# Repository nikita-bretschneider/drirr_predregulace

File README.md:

# Poznámky k návrhu desky skokové předregulace

## Změny v konstrukci

Konstrukce není moje. Hodnoty součástek jsou uvedeny pouze tam, kde byly známy (platí pro schéma i silkscreeny). Jediná konstrukční změna je přidání tranzistoru *Q1*, protože proudová zatížitelnost výstupu *LM311* je pouze *50mA*, což stačí na malé relé, avšak chci otevřít možnost použít automobilní relé, jehož pozitivní vlastností je že se nerozteče při trvalém sepnutí. Bohužel si dokáže vzít až *140mA*. PNP tranzistor používám z toho důvodu, aby nebylo nutno měnit logiku spínání. *LM311* sama o sobě spíná v záporném pólu, pokud se aktivuje spínání tranzistorem, spíná se v kladném pólu, vlastní *LM311* spíná pouze bázový proud tranzistoru *Q1*. Použití tohoto tranzistoru je optional a konfiguruje se při osazení propojkami *J4*, *J5* a *J6*. Původní zapojení, tj. bez tranzistoru *Q1*, se aktivuje neosazením *Q1* a *R6*, dále se spojí *J5* a *J6*. Propojka *J4* zůstává rozpojená. Pro použití tranzistoru *Q1* (například při použití automobilního relé) se osadí *R6*, *Q1* a propojí se propojka *J4*. Propojky *J5* a *J6* zůstávají rozpojené.

## Použití pojmenovaných signálů a propojovací definice

Použití pojmenovaných signálů umožňuje rozdělit schéma do funkčních bloků a tak jej zpřehlednit. Separátní definice připojovacích míst k signálům umožňuje snadno měnit pinout jednotlivých konektorů s ohledem na situaci na desce, neb docházelo k optimalizaci na snadnou výrobu a minimální cenu desky. Dále takový postup vytváří přehledný pinout všech použitých konektorů na jediném místě dokumentace, což opět poslouží přehlednosti.

## Vlastní návrh desky, možné problémy, prokovy

Vlastní návrh desky je proveden tak, aby byl výrobně jednoduchý. Desku lze nechat vyrobit jak s prokovy tak bez nich. V obou případech lze za slabé místo považovat kondenzátory *C1* a *C2*, kde je jeden z pólů přístupný do rozlité země (vedení *ACS0*) pouze přes prokov. Vzhledem k zátěži celého pomocného zdroje řádově ve stovkách mA (a z toho plynoucích cirkulačních proudů maximálně ve stovkách mA) to nepovažuji za problém. Větší problém nastává při pájení *C1* a *C2* do desky bez prokovů, kde nelze pájet z horní strany kvůli překrytí vrstvý pouzdrem součástky. Pro tento případ je na spodní straně připravena rozlitá plocha mědi, kdy lze provést propojení s vrchní stranou (stranou součástek) pomocí vývodů jiných součástek, případně na vhodném místě navrtat via.

Desku lze též vyrobit svépomocí, kdy se strana spojů vyrobí například metodou *toner transfer*, přičemž horní strana obsahuje toliko rozlitou měď (s vyjímkou jednoho jumperu, který lze ignorovat, viz níže), čili před leptáním se vykryjí problematická místa (pod pojistkami a pod částmi konektorů) lakýrnickou páskou, celou horní strana se poté přestříká leptuvzdorným lakem a po zaschnutí se odstraní lakýrnická páska. Pro spodní stranu se použije buď metoda toner transfer, nebo fotocesta. V případě toner transferu doporučuji začít spodní stranou, v případě fotocesty doporučuji obrácený postup.  Po odleptání a odvrtání ze spodní strany se z horní  strany následně odstraní měděná plocha v okolí děr buď odfrézováním, nebo zcela jednoduše pomocí mělkého odvrtání tlustým vrtákem. Neodvrtávají se místa, kde je součástka spojena se zemní plochou. V těchto místech se potom pájí z obou stran. Problémem jednoduché výroby je jumper *J4*, který  je ze stramy součástek a při prostém ponechání měděné vrstvy jednoduše nebude existovat. Nepovažuji to však za problém, protože konfigurace se provádí při osazení a později ji již není možné změnit, čili pokud se osazuje *Q1*, potom se neodfrézuje/neodvrtá měděná vrstva kolem anody *D8* a tato se připájí z obou stran. *J6* a *J5* se potom neosazuje. V opačném případě se okolí anody *D8* odfrézuje, *Q1* a *R6* se neosadí, *D8* se zapájí jen z jedné strany a propojí se *J6* a *J5*.

## Proč není na desce relé

Protože otevřenost variabilitě, protože míním použít automobilní relé, které má vlastní držák a vývody na fastonech, v neposlední řadě proto, že se tím zmenší deska. Navíc to vytváří určitou variabilitu v zapojení předregulace, tj. lze například přepínat mezi dvoucestným usměrněním a násobičem, což otevírá možnost použít transformátor, který náhodou máte, namísto nákupu nějakého konkrétního. Celá deska je navrhovaná s ohledem na maximální možnou variabilitu, je zcela nevhodná pro seriovou výrobu včetně maloseriové, takže je pochopitelně nevhodná i pro strojové osazení.

## Proč se používají svorkovnice

V původní konstrukci byly fastony a osobně v nich vidím problém. Ten konektor chce značnou sílu pro zapojení i vypojení, přičemž tato deska byla navrhovaná nejen na maximální variabilitu, ale také na možnost snadné výroby, do které musím bohužel zahrnout nejen pochybné lamináty, ale též kuprokart a jiné hrůzy. Kombinace kuprokartu a fastonu znamená zlomenou desku. Spolehlivě. Svorkovnice ale funguje, protože se na desku příliš netlačí. Pochopitelně na jejím místě lze osadit víceméně leccos, co roztečí odpovídá. Svorkovnice jsou na desce dvě čtyřpólové a jedna dvoupólová. Spojit je všechny do jedné velké svorkovnice není dobrý nápad, toner transfer občas způsobí mírné ujetí rozměrů, což by pro tak velký pevný kus bylo fatální. Svorkovice je tedy rozdělena na tři logické části — propojení s řídící deskou zdroje, čili pomocné napájení *±12V* a *sense* vstup, svorkovnici pro připojení cívky relé a svorkovnici pro připojení pomocného transformátoru. Tato je zvolena čtyřpinová ze dvou důvodů. Především dvoupinové svorkovnice lze stohovat na čtyřpólové, takže tato volba znamená, že koupíte pět dvoupólových (a dostanete množstevní slevu, což by vás při nákupu jedné třípólové nepotkalo), dále transformátor může mít dvě oddělená sekundární vinutí, proto je střed vyveden dvakrát.

## Použití pomocného transformátoru s jediným sekundárním vinutím

Pokud máte pomocný transformátor jen s jediným vinutím bez vyvedeného středu, neosadí se *F1*, *D1*, *D4* a polovina svorkovnice *J3*. Dále je nutno zvětšit kapacity *C1* a *C2* na minimálně dvojnásobek.Transformátor potom pracuje v lichých půlvlnách do jedné větve a v sudých do druhé. Toto řešení však příliš nedoporučuji.

## Závěr, varování

Konstrukce není moje, desky nevyrábím, pokud si někde chcete zadat výrobu, je to váš problém, odmítám za to nést jakoukoliv odpovědnost. Chyby se stávají, to je realita. Vše si důkladně zkontrolujte a rozmyslete před tím, než začnete desku vyrábět.

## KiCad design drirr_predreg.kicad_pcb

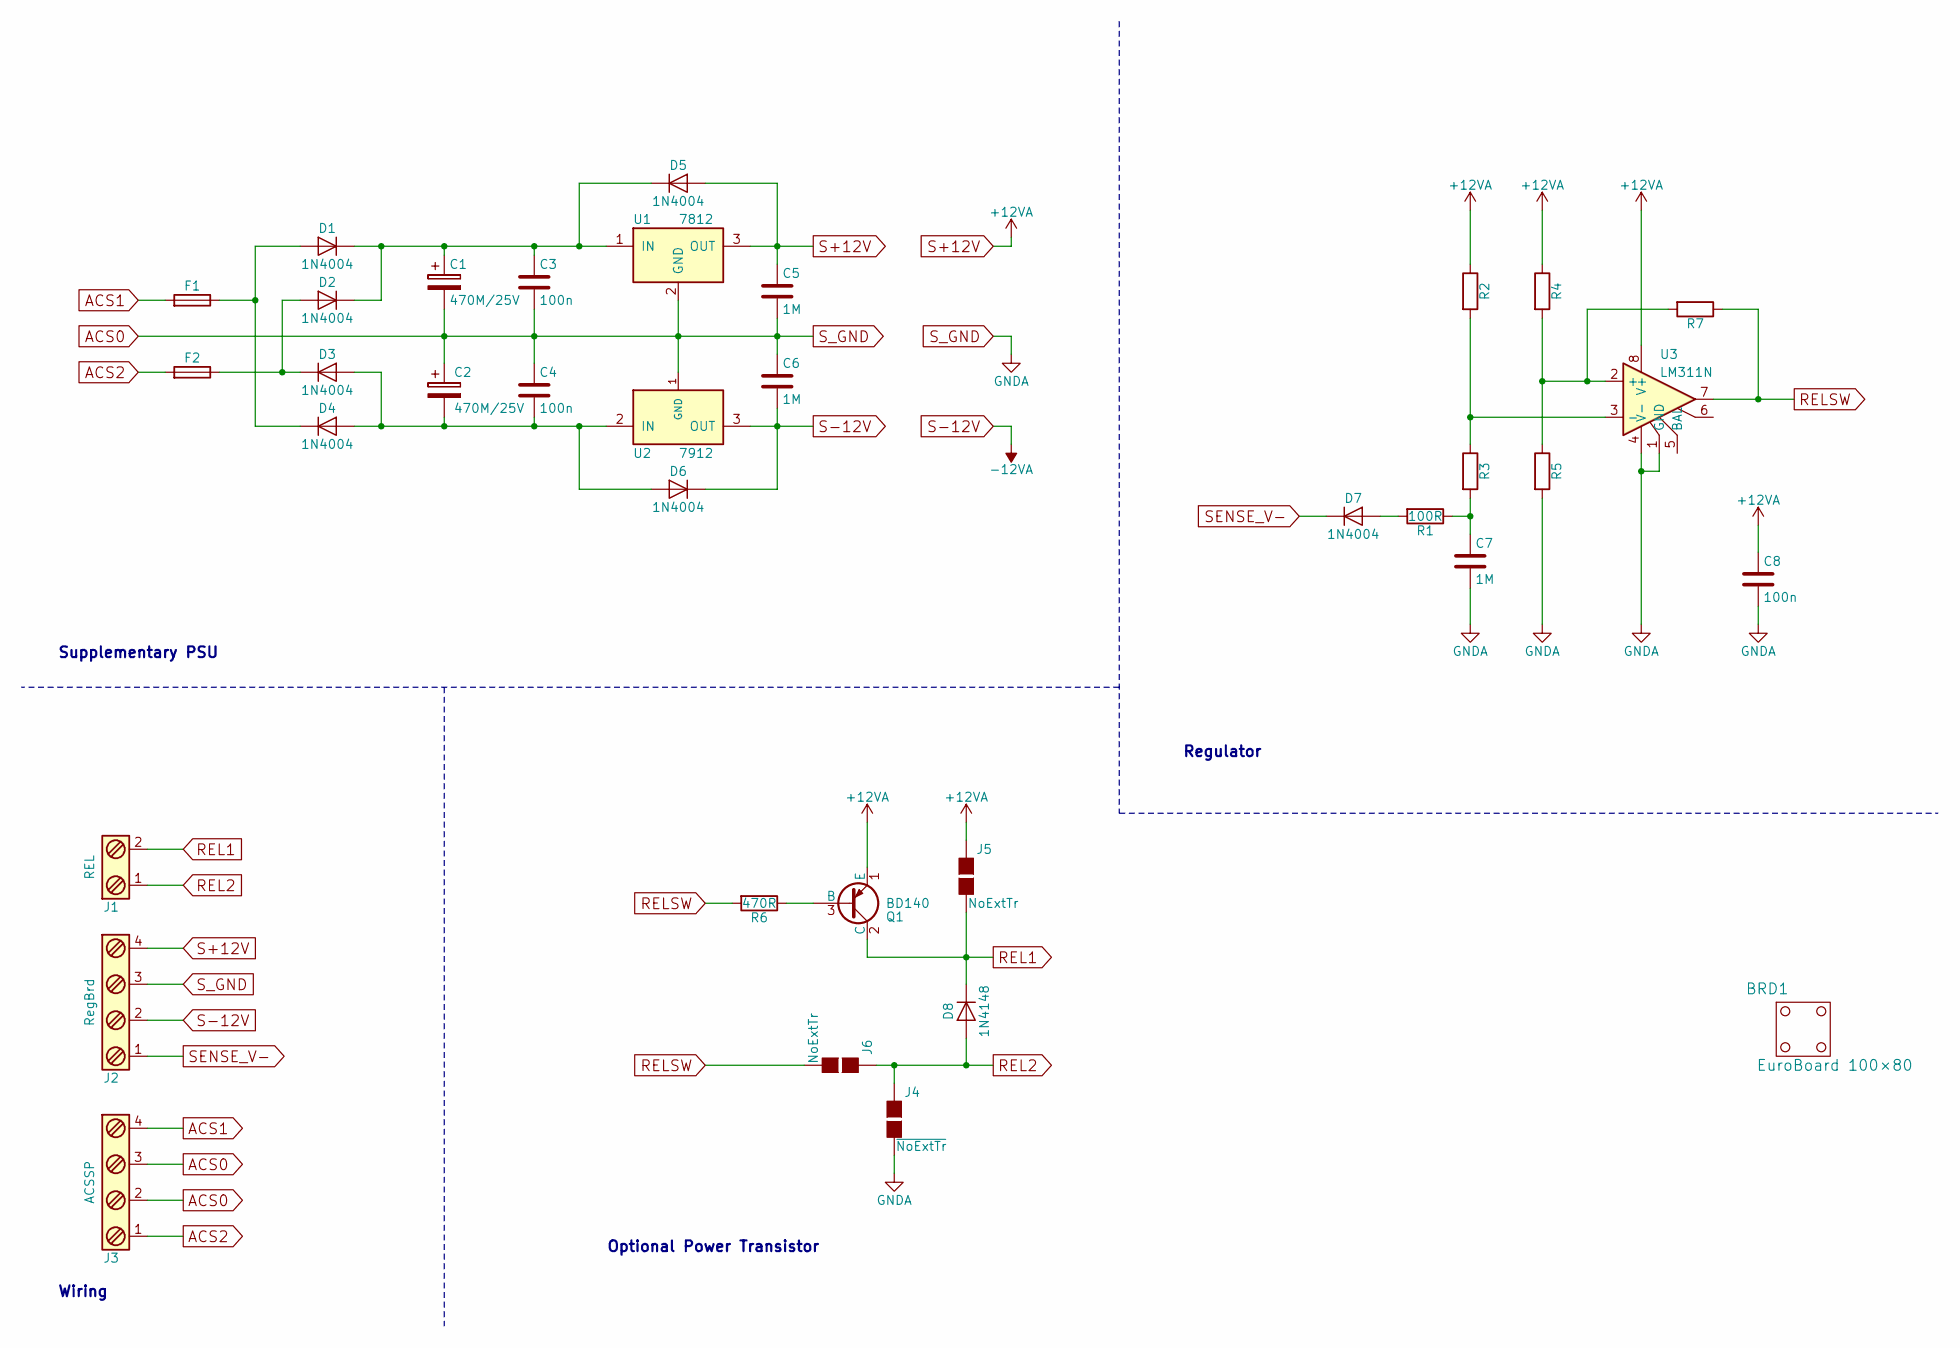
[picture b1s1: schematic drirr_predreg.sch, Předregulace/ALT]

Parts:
BRD1: EuroBoard 100×80; EuroBoard_halb_Type-I_100mmX80mm_holes
C1, C2: 470M/25V; CP_Radial_D12.5mm_P5.00mm
C3, C4, C8: 100n; C_Disc_D7.5mm_W2.5mm_P5.00mm
C5, C6, C7: 1M; C_Disc_D7.5mm_W2.5mm_P5.00mm
D1, D2, D3, D4, D5, D6, D7: 1N4004; D_DO-15_P12.70mm_Horizontal
D8: 1N4148; D_DO-15_P12.70mm_Horizontal
F1, F2: Fuse; Fuseholder5x20_horiz_open_universal_Type-III
J1: REL; AK300-2
J2: RegBrd; AK300-4
J3: ACSSP; AK300-4
J4: ~NoExtTr; GS2
J5, J6: NoExtTr; GS2
Q1: BD140; TO-126_Vertical
R1: 100R; R_Axial_DIN0411_L9.9mm_D3.6mm_P15.24mm_Horizontal
R2, R3, R4, R5, R7: R; R_Axial_DIN0411_L9.9mm_D3.6mm_P15.24mm_Horizontal
R6: 470R; R_Axial_DIN0411_L9.9mm_D3.6mm_P15.24mm_Horizontal
U1: 7812; TO-220_Vertical
U2: 7912; TO-220_Vertical
U3: LM311N; DIP-8_W7.62mm_LongPads

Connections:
ACS0: C1.2, C2.1, C3.2, C4.1, C5.2, C6.1, C7.2, C8.2, J2.3, J3.2, J3.3, J4.2 (G2), R5.2, U1.2 (GND), U2.1 (GND), U3.1 (GND), U3.4 (V-)
ACS1: F1.2, J3.4
ACS2: F2.2, J3.1
unnamed: C1.1, C3.1, D1.1 (K), D2.1 (K), D5.1 (K), U1.1 (IN)
unnamed: C2.2, C4.2, D3.2 (A), D4.2 (A), D6.2 (A), U2.2 (IN)
unnamed: C7.1, R1.1, R3.2
unnamed: D1.2 (A), D4.1 (K), F1.1
unnamed: D2.2 (A), D3.1 (K), F2.1
unnamed: D7.2 (A), R1.2
unnamed: Q1.3 (B), R6.1
unnamed: R2.2, R3.1, U3.3 (-)
unnamed: R4.2, R5.1, R7.2, U3.2 (+)
REL1: D8.1 (K), J1.2, J5.2 (G2), Q1.2 (C)
REL2: D8.2 (A), J1.1, J4.1 (G1), J6.1 (G1)
RELSW: J6.2 (G2), R6.2, R7.1, U3.7
S+12V: C5.1, C8.1, D5.2 (A), J2.4, J5.1 (G1), Q1.1 (E), R2.1, R4.1, U1.3 (OUT), U3.8 (V+)
S-12V: C6.2, D6.1 (K), J2.2, U2.3 (OUT)
SENSE_V-: D7.1 (K), J2.1

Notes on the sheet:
Supplementary PSU
Wiring
Regulator
Optional Power Transistor

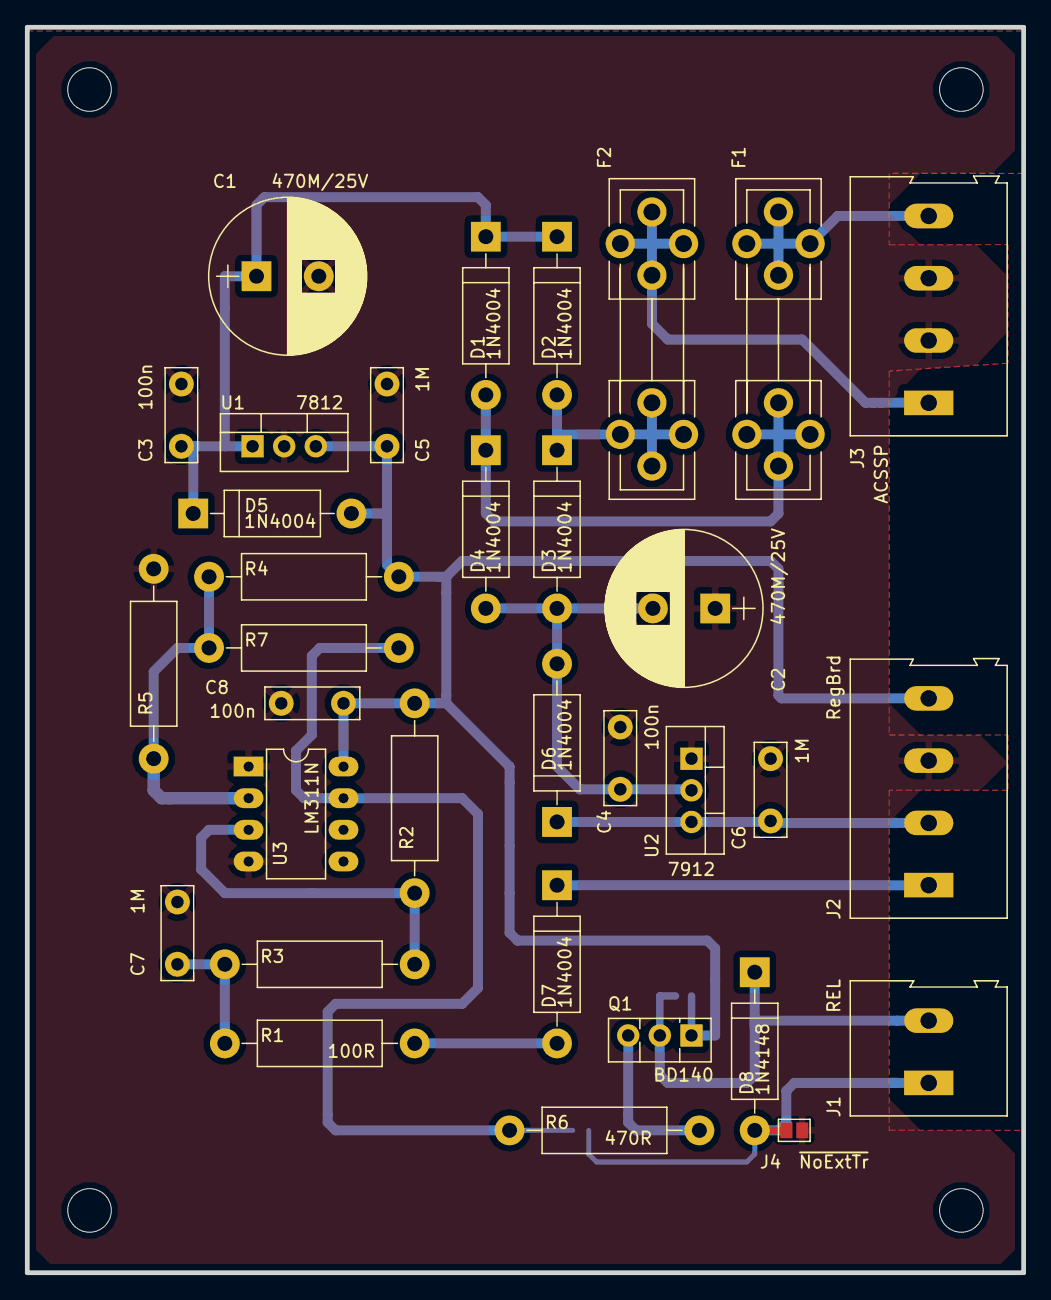
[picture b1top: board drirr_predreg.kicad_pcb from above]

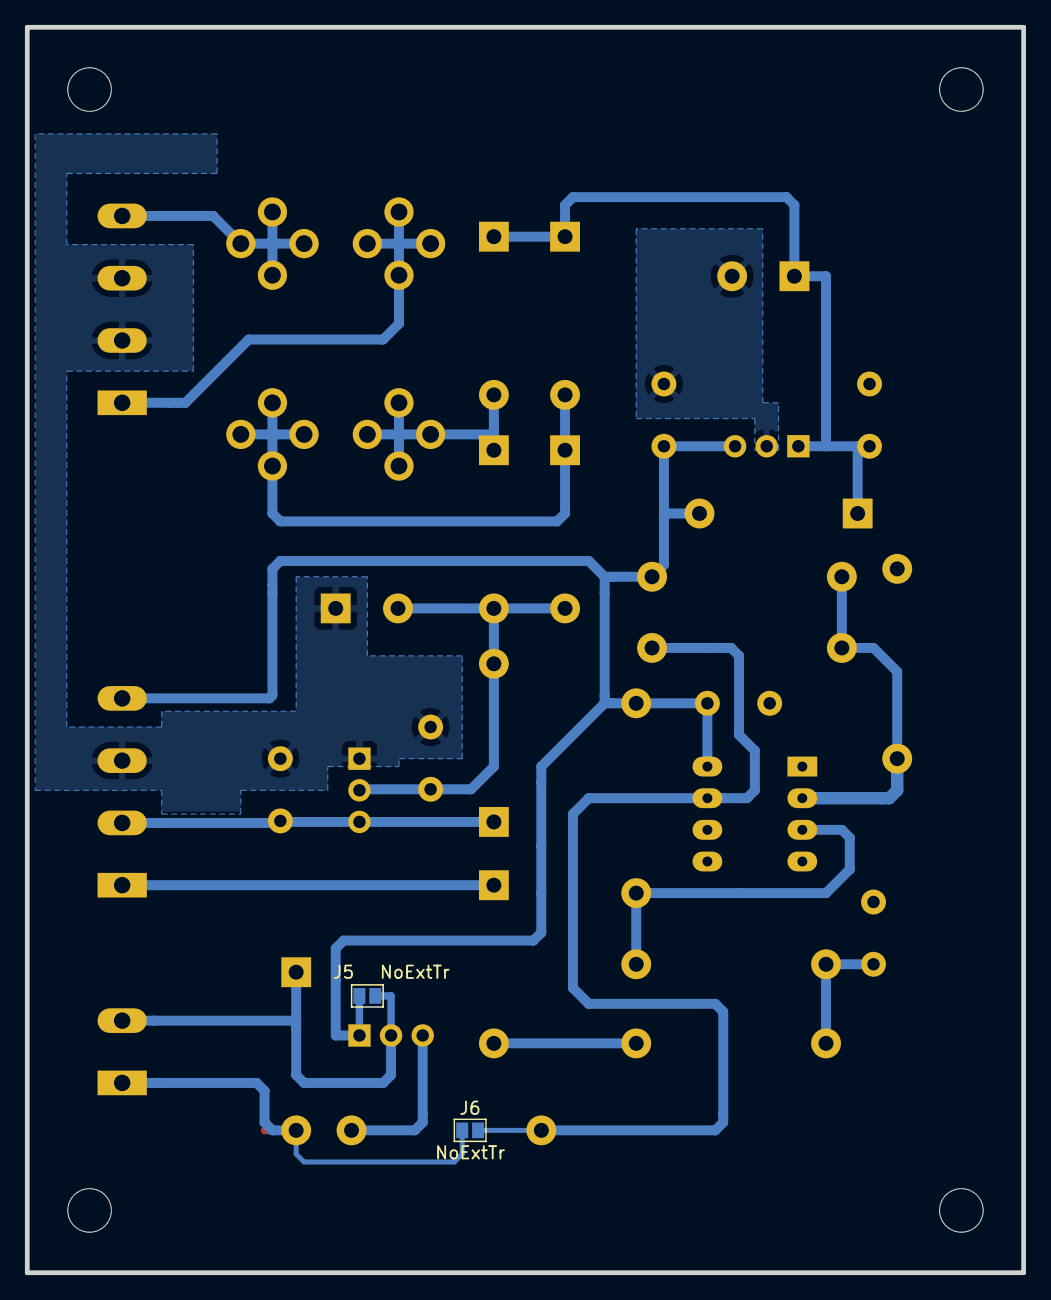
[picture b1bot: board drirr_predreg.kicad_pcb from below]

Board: 2 copper layers, 80.0 x 100.0 mm, 36 parts (2 on the bottom side), 18 nets.

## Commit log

2021-04-29 rev01a_cmt1
